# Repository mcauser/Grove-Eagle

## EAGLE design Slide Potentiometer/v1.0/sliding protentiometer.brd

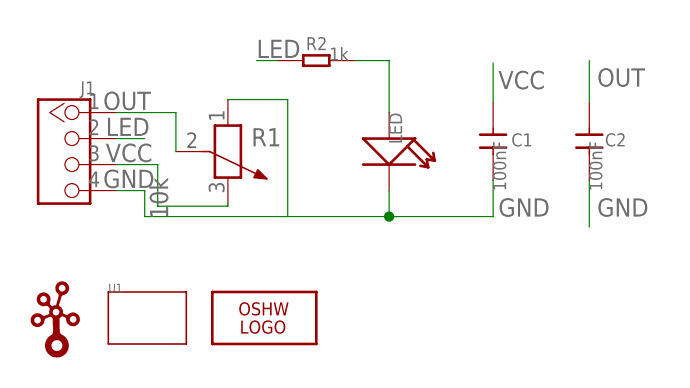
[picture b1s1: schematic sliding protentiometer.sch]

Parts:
C1, C2: 100nF; 0805
J1: TWIG-4P-2.0-2.0; 4P-2.0
LED: LED'0805'; LED-0805
LOGO1: LOGO-OSHW-FILLX0200-NT; OSHW_FILLX200_NOTEXT
R1: 10k; 3P-SQUA-45.6X10X5.8H
R2: 1k; 0805
U1: TWIG'3U'; 3U-DIM-W/-DRILL
U$1: LOGO-TWIG; TWIGLOGO

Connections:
GND: C1.2, C2.2, J1.4, LED.-, R1.1
LED: J1.2, R2.1
unnamed: LED.+, R2.2
OUT: C2.1, J1.1, R1.2 (3)
VCC: C1.1, J1.3, R1.3 (2)

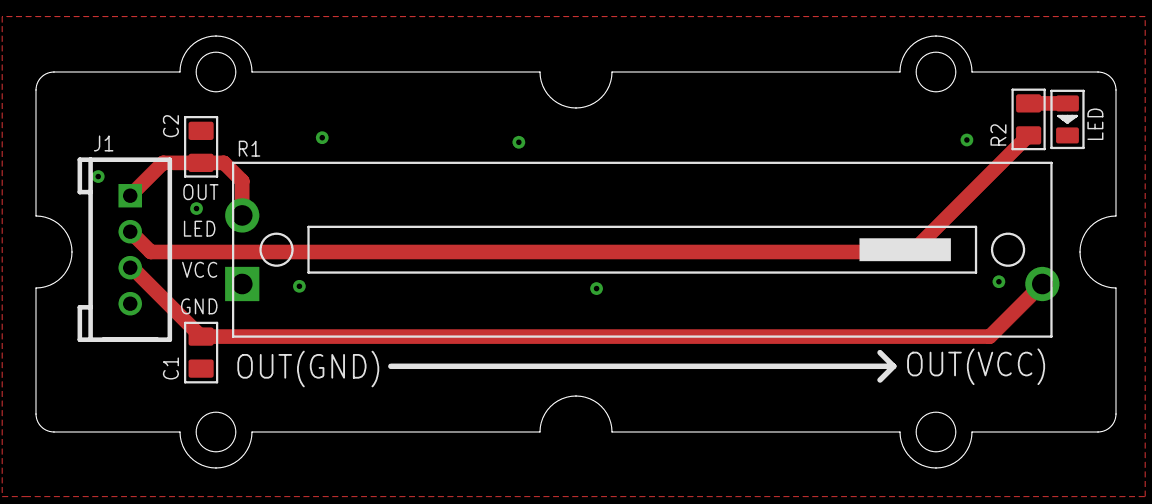
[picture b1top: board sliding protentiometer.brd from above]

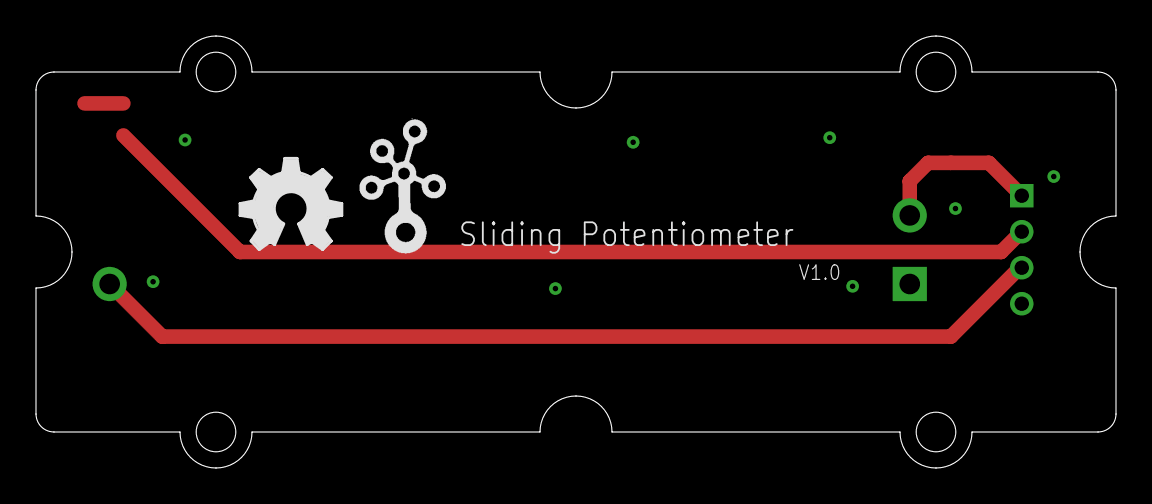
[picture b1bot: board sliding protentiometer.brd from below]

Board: 2 copper layers, 60.0 x 24.0 mm, 9 parts (2 on the bottom side), 5 nets.

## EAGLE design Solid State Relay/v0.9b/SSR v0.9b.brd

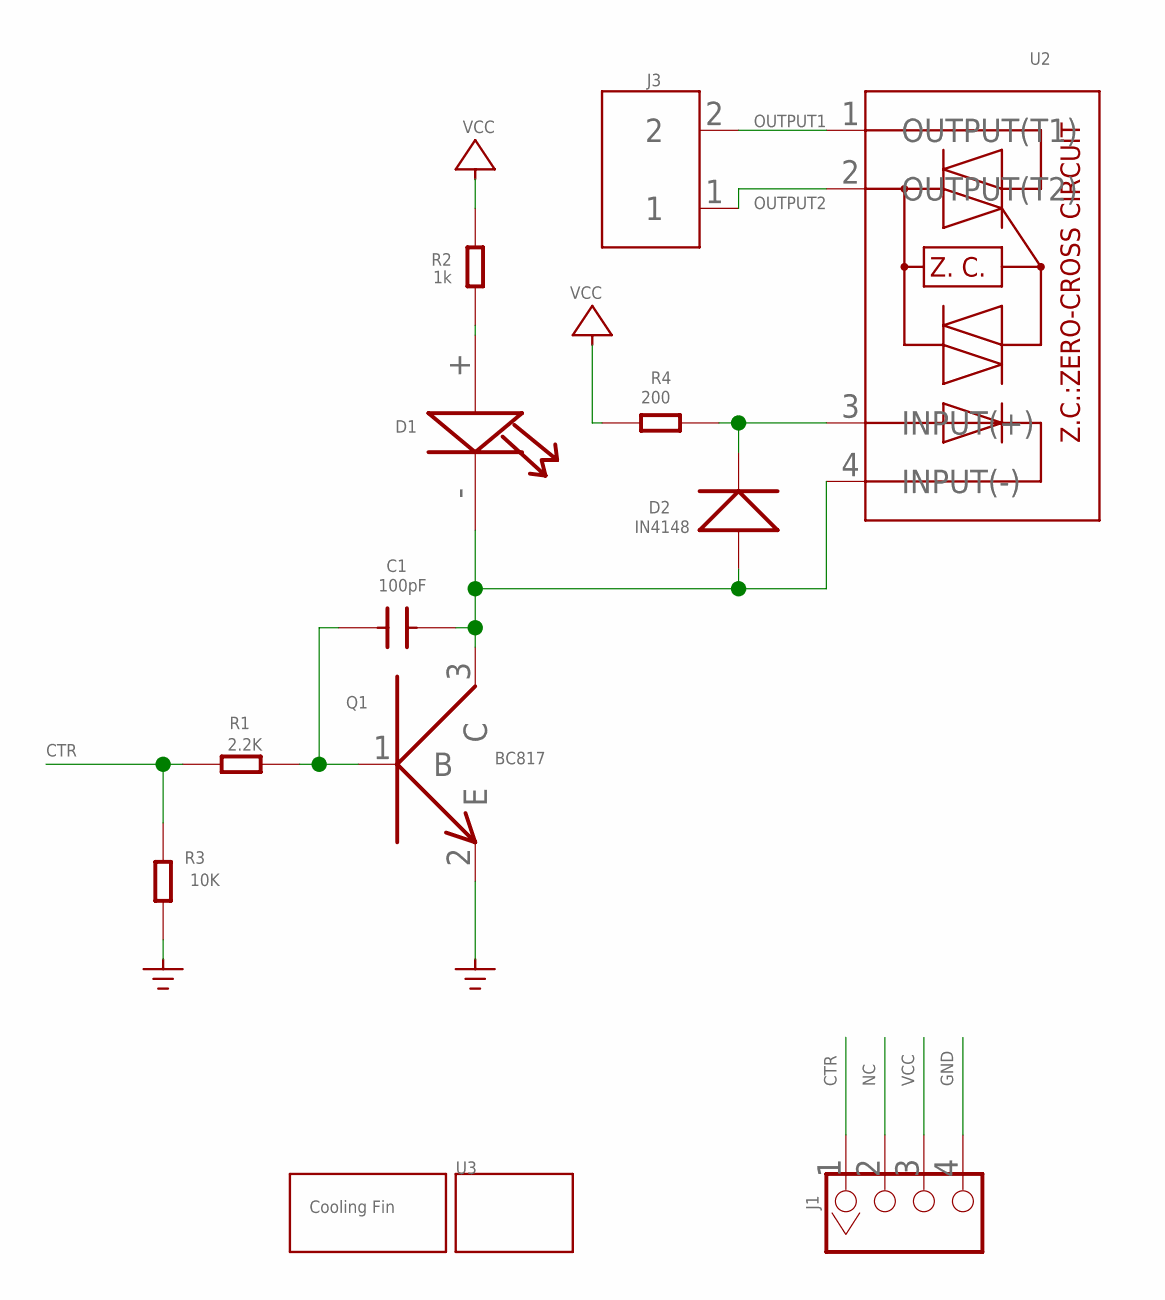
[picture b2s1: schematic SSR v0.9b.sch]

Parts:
C1: 100pF; 0603
D1: LED0805
D2: IN4148; DO-35-SMD
J1: TWIG-4P-2.0-2.0; 4P-2.0
J3: SCREW-TERMINAL-2P5.0; 2P-5.0
Q1: NPN_9013; SOT23
R1: 2.2K; 0603
R2: 1k; 0603
R3: 10K; 0603
R4: 200; 0603
U1: SILK-COOLING-FIN; COOLING-FIN-30X25
U2: RELAY-S208T02; 4P-23X4X16H
U3: TWIG-2X2U; 2X2U-DIM-W/-DRILL

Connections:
CTR: J1.1, R1.1, R3.2
GND: J1.4, Q1.2 (E), R3.1
unnamed: D2.C (-), R4.2, U2.3 (INPUT(+))
unnamed: C1.2, Q1.1 (B), R1.2
unnamed: C1.1, D1.-, D2.A (+), Q1.3 (C), U2.4 (INPUT(-))
unnamed: D1.+, R2.1
NC: J1.2
OUTPUT1: J3.2, U2.1 (OUTPUT(T1))
OUTPUT2: J3.1, U2.2 (OUTPUT(T2))
VCC: J1.3, R2.2, R4.1

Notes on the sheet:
BC817

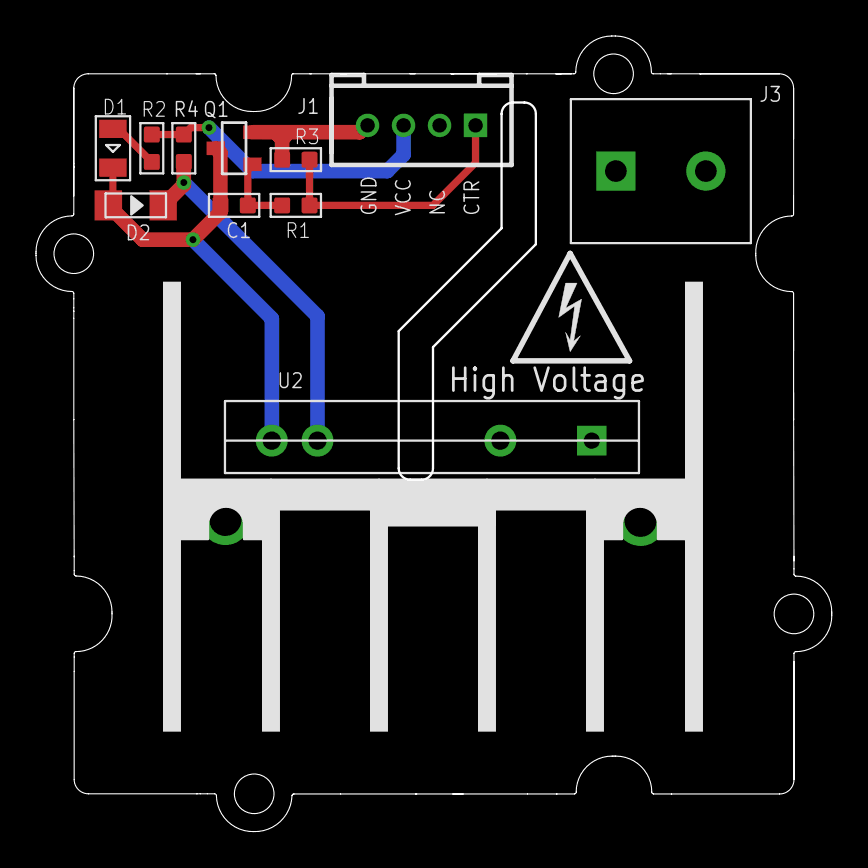
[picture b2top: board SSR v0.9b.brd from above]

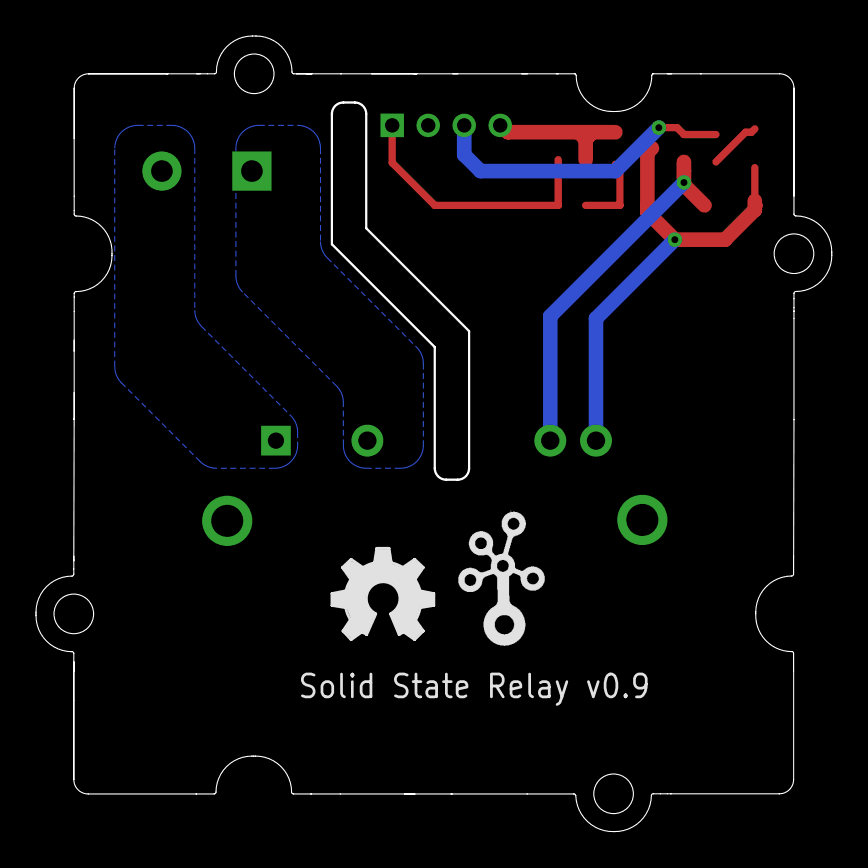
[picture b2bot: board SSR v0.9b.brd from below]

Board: 2 copper layers, 44.2 x 44.2 mm, 15 parts (2 on the bottom side), 9 nets.

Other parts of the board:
U$1: TWIGLOGO
U$2: OSHW_FILLX200_NOTEXT

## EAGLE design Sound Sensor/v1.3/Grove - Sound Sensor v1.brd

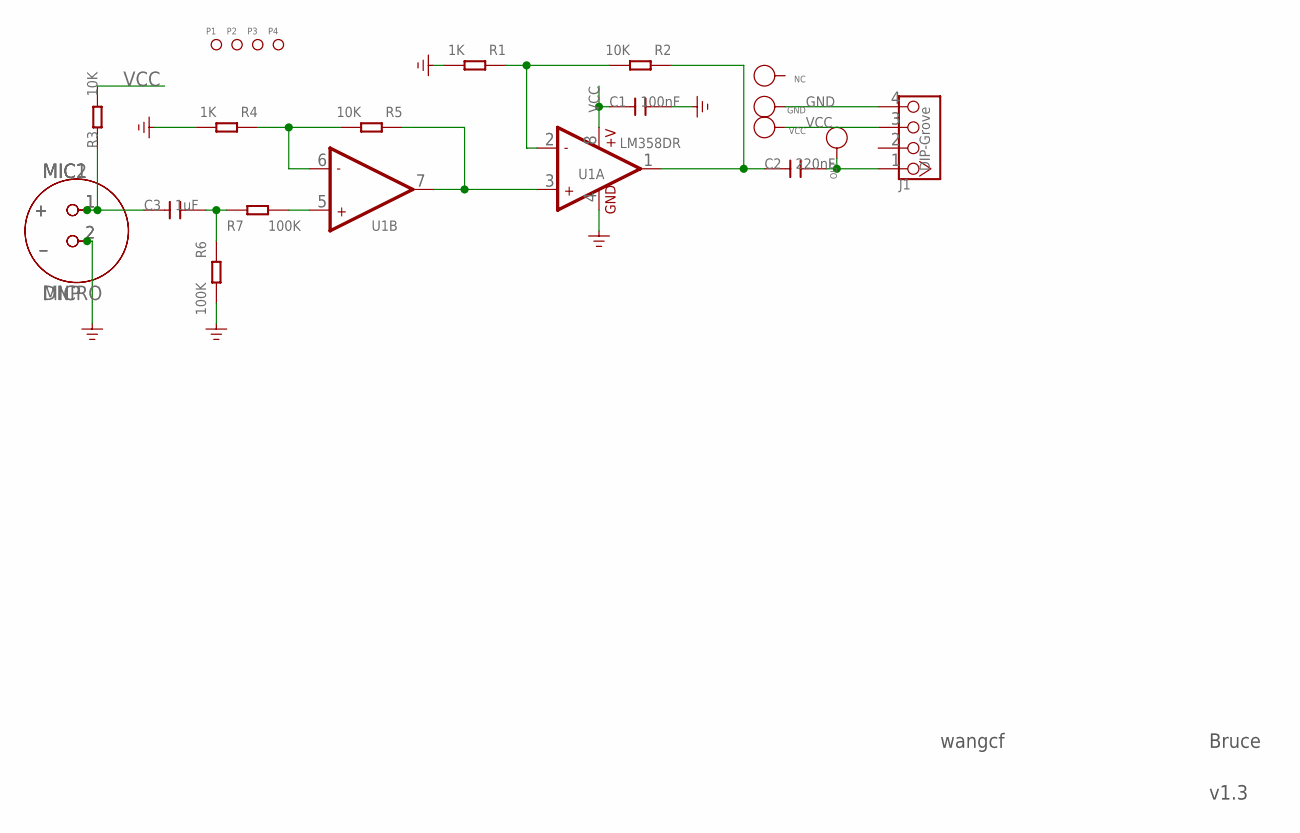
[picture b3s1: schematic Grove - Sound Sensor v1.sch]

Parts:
C1: 100nF; C0603
C2: 220nF; C0603
C3: 1uF; C0603
GND: PAD-TEST-POINT'4545'; TP_4545
J1: DIP-Grove; 4P-2.0
MIC1: MICRO
MIC2: DNP; MICRO
NC: PAD-TEST-POINT'4545'; TP_4545
OUT: PAD-TEST-POINT'4545'; TP_4545
P1, P2, P3, P4: PAD-MARK; ROUND-MARK-1.0
R1, R4: 1K; R0603
R2, R3, R5: 10K; R0603
R6, R7: 100K; R0603
U1: LM358DR; SO08
VCC: PAD-TEST-POINT'4545'; TP_4545

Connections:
GND: C1.2, GND.T, J1.4, MIC1.2 (_), MIC2.2 (_), R1.2, R4.2, R6.2, U1.4 (GND)
unnamed: R7.2, U1.5 (+IN2)
unnamed: R4.1, R5.2, U1.6 (-IN2)
unnamed: C3.2, R6.1, R7.1
unnamed: C3.1, MIC1.1 (+), MIC2.1 (+), R3.1
unnamed: R5.1, U1.3 (+IN1), U1.7 (OUT2)
unnamed: R1.1, R2.2, U1.2 (-IN1)
OUT: C2.2, J1.1, OUT.T
OUT1: C2.1, R2.1, U1.1 (OUT1)
VCC: C1.1, J1.3, R3.2, U1.8 (+V), VCC.T

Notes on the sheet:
wangcf
Bruce
v1.3

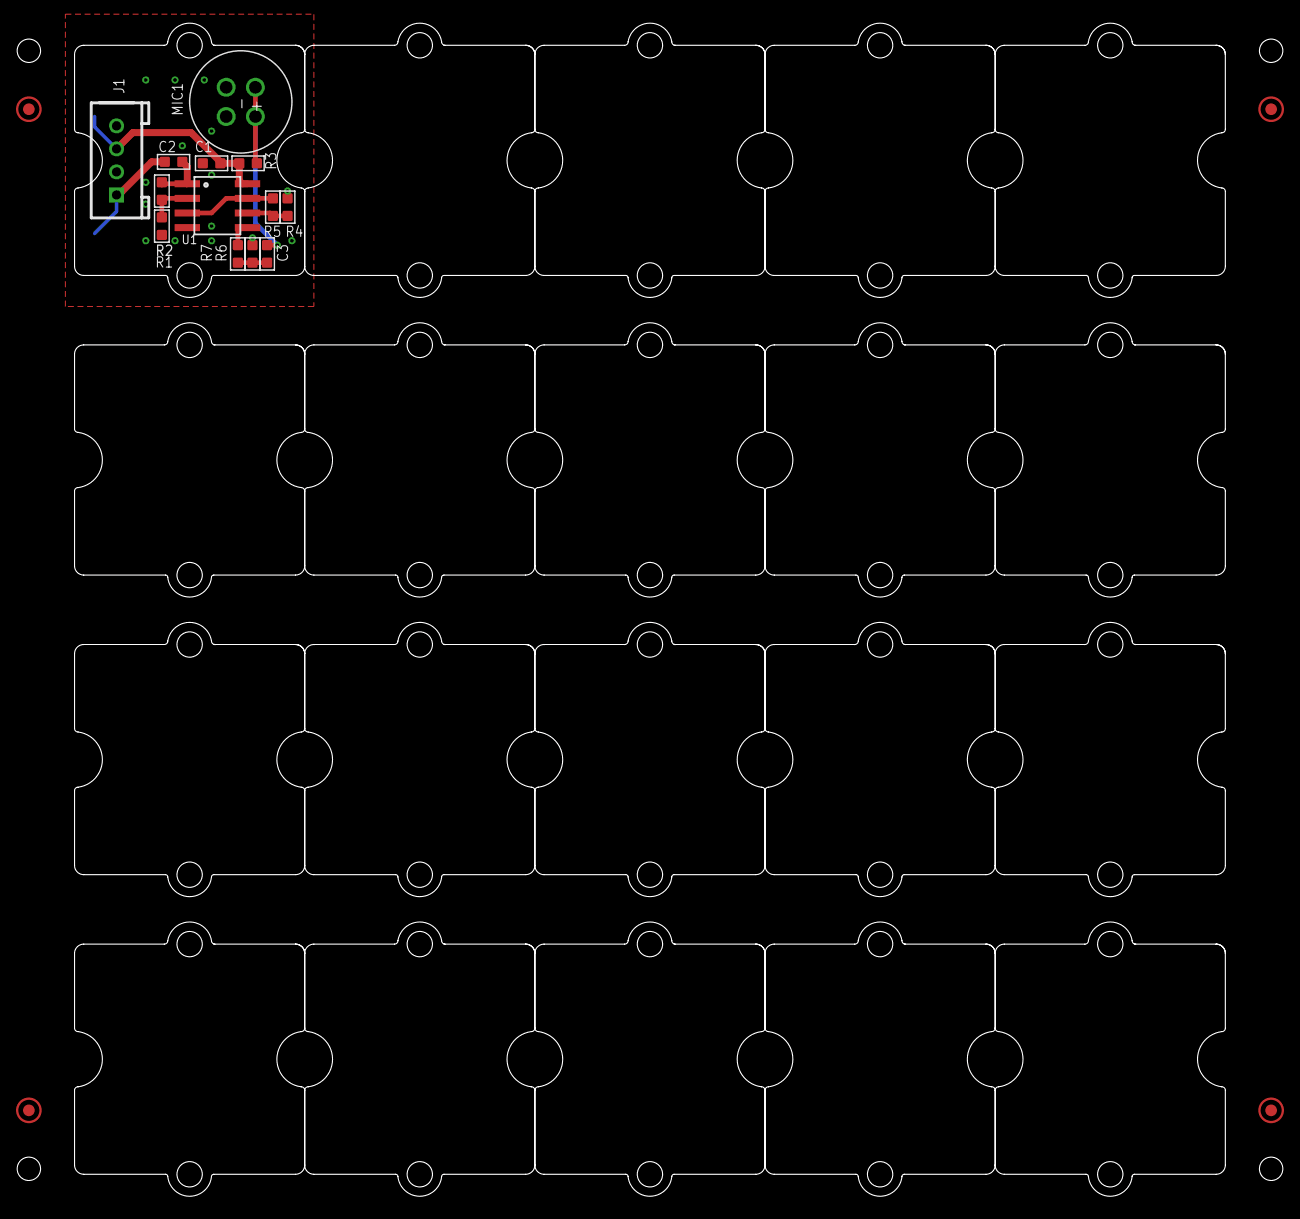
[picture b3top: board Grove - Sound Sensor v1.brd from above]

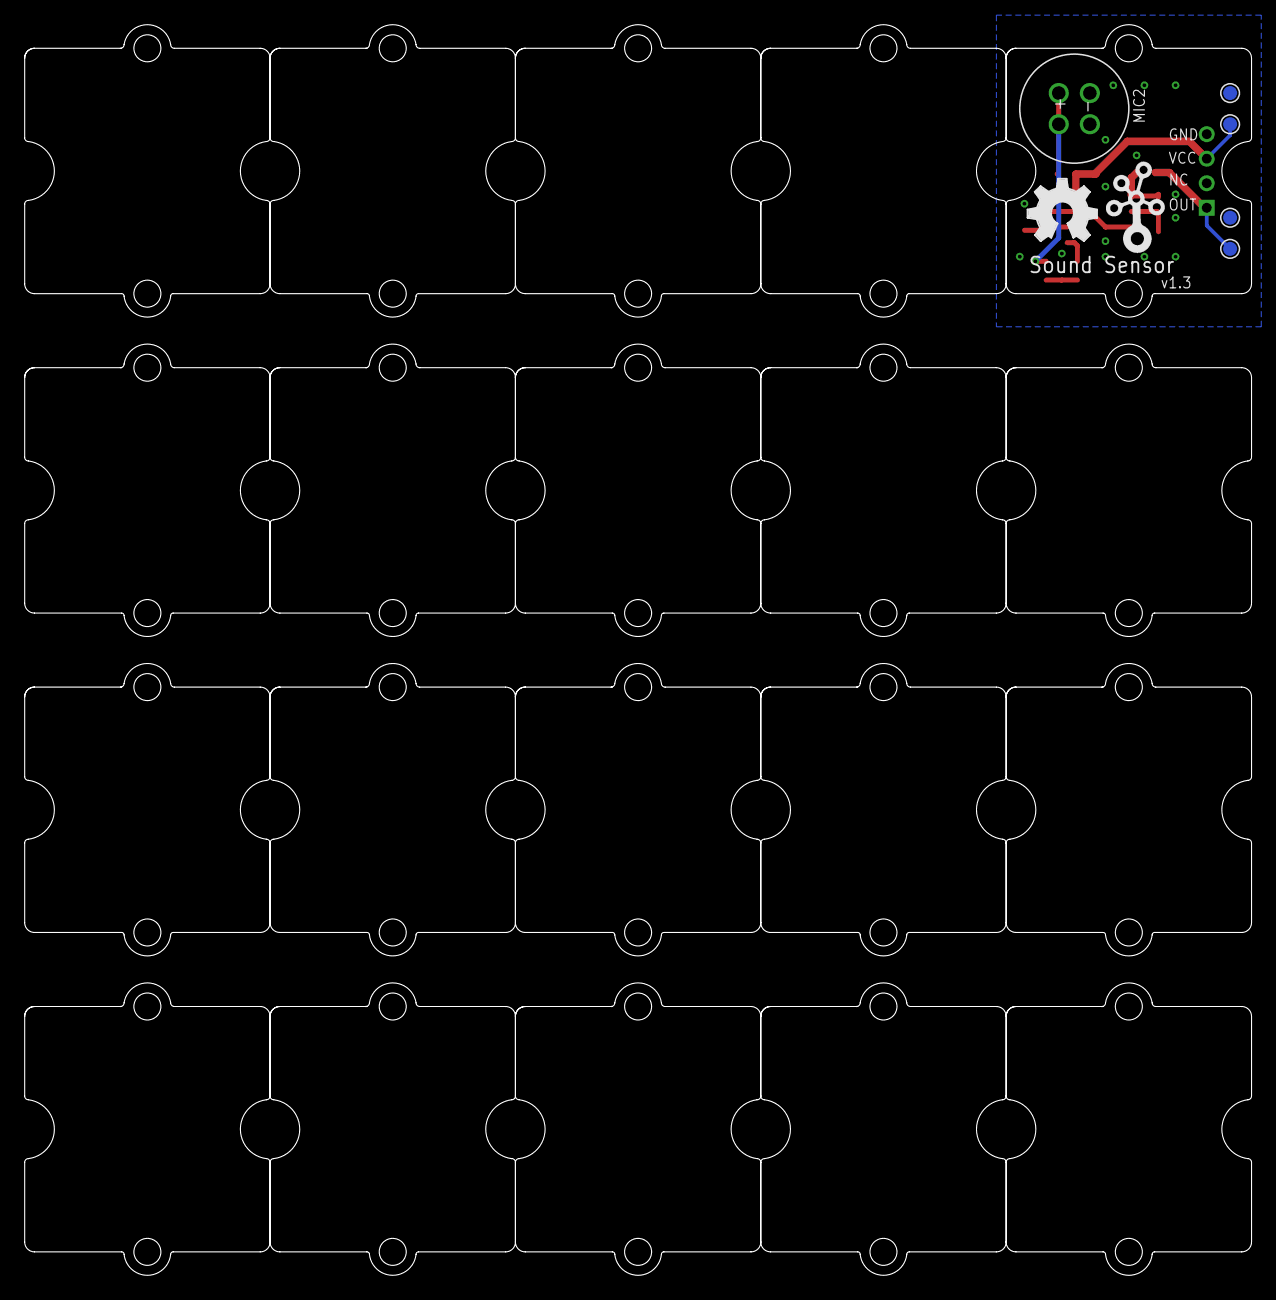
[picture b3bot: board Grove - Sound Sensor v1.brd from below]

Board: 2 copper layers, 100.0 x 101.9 mm, 44 parts (7 on the bottom side), 10 nets.

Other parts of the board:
U$1: OSHW_FILLX200_NOTEXT
U$4, U$12, U$13, U$14, U$15, U$16, U$17, U$18, U$19, U$20, U$21, U$22, U$23, U$24, U$25, U$26, U$27, U$28, U$29, U$30: 1U-DIM-W/-DRILL
U$7: TWIGLOGO

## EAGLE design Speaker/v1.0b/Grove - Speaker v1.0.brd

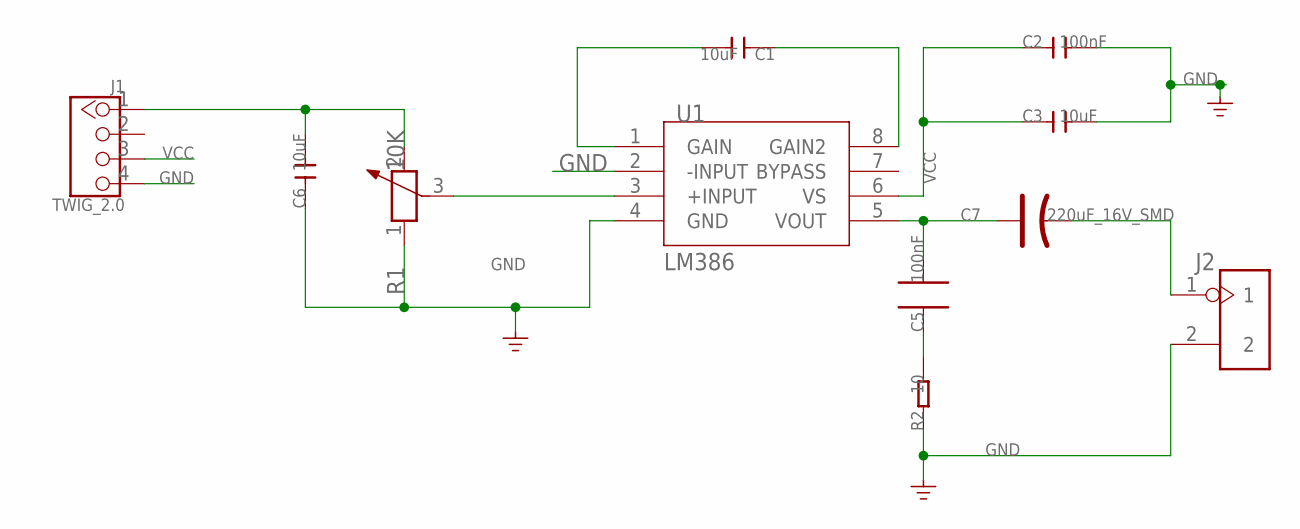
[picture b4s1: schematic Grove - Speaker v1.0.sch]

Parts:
C1, C3, C6: 10uF; C0805
C2: 100nF; C0603
C5: 100nF; 0603
C7: 220uF_16V_SMD; ELECTRO-SMD-E-7.8MM
J1: TWIG_2.0; 2.0_1X4
J2: HEADER-2P-2.0; 2P-2.0
R1: 10K; 3P-SQUA-7X6.8
R2: 10; R0603
U1: LM386; SO08

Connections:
GND: C2.2, C3.2, C6.1, J1.4, J2.2, R1.1, R2.1, U1.2 (-INPUT), U1.4 (GND)
unnamed: C5.1, R2.2
unnamed: C1.1, U1.8 (GAIN2)
unnamed: C7.-, J2.1
unnamed: R1.3, U1.3 (+INPUT)
unnamed: C6.2, J1.1, R1.2
unnamed: C5.2, C7.+, U1.5 (VOUT)
unnamed: C1.2, U1.1 (GAIN)
VCC: C2.1, C3.1, J1.3, U1.6 (VS)

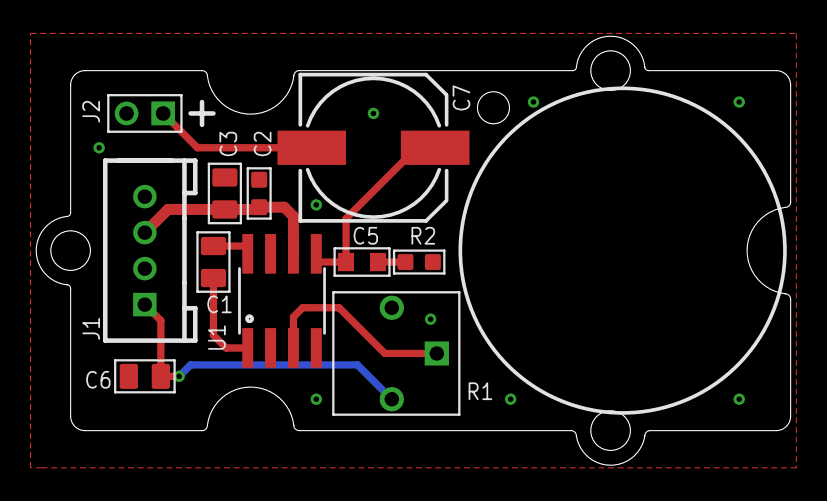
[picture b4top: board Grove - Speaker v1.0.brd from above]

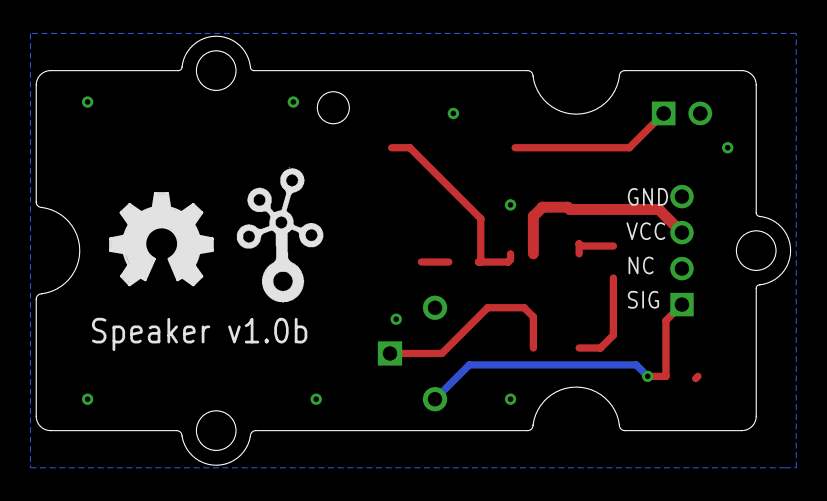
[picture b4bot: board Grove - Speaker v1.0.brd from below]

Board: 2 copper layers, 41.9 x 23.8 mm, 14 parts (2 on the bottom side), 9 nets.

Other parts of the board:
U$2: 2U-DIM-W/DRILL
U$3: OSHW_FILLX200_NOTEXT
U$4: TWIGLOGO

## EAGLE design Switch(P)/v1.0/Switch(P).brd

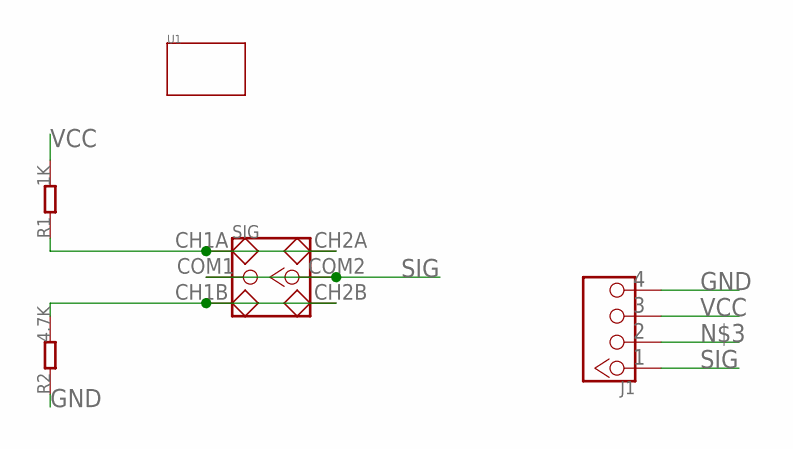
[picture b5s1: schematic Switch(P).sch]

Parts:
J1: TWIG-4P-2.0-2.0; 4P-2.0
R1: 1K; 0603
R2: 4.7K; 0603
SIG: SWITCH-2CH-6P; 6P-2CH-2.54-7.6X3.0
U1: TWIG-1U; 1U-DIM-W/-DRILL

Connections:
GND: J1.4, R2.1
unnamed: R1.1, SIG.CH1A, SIG.CH2A
unnamed: R2.2, SIG.CH1B, SIG.CH2B
SIG: J1.1, SIG.COM1, SIG.COM2
VCC: J1.3, R1.2

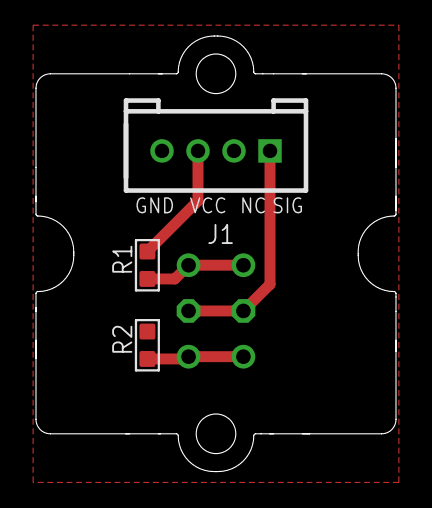
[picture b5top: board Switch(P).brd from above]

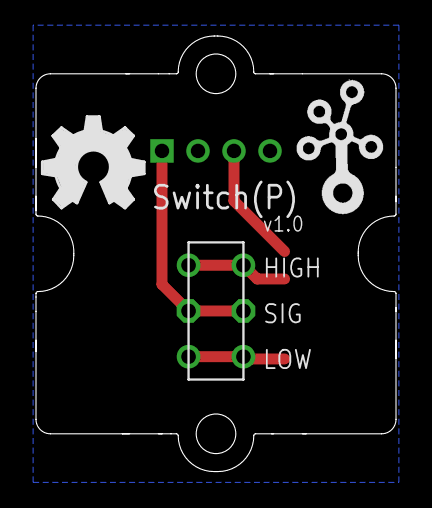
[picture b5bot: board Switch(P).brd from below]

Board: 2 copper layers, 20.0 x 24.2 mm, 7 parts (3 on the bottom side), 5 nets.

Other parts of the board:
U$1: TWIGLOGO
U$2: OSHW_FILLX200_NOTEXT

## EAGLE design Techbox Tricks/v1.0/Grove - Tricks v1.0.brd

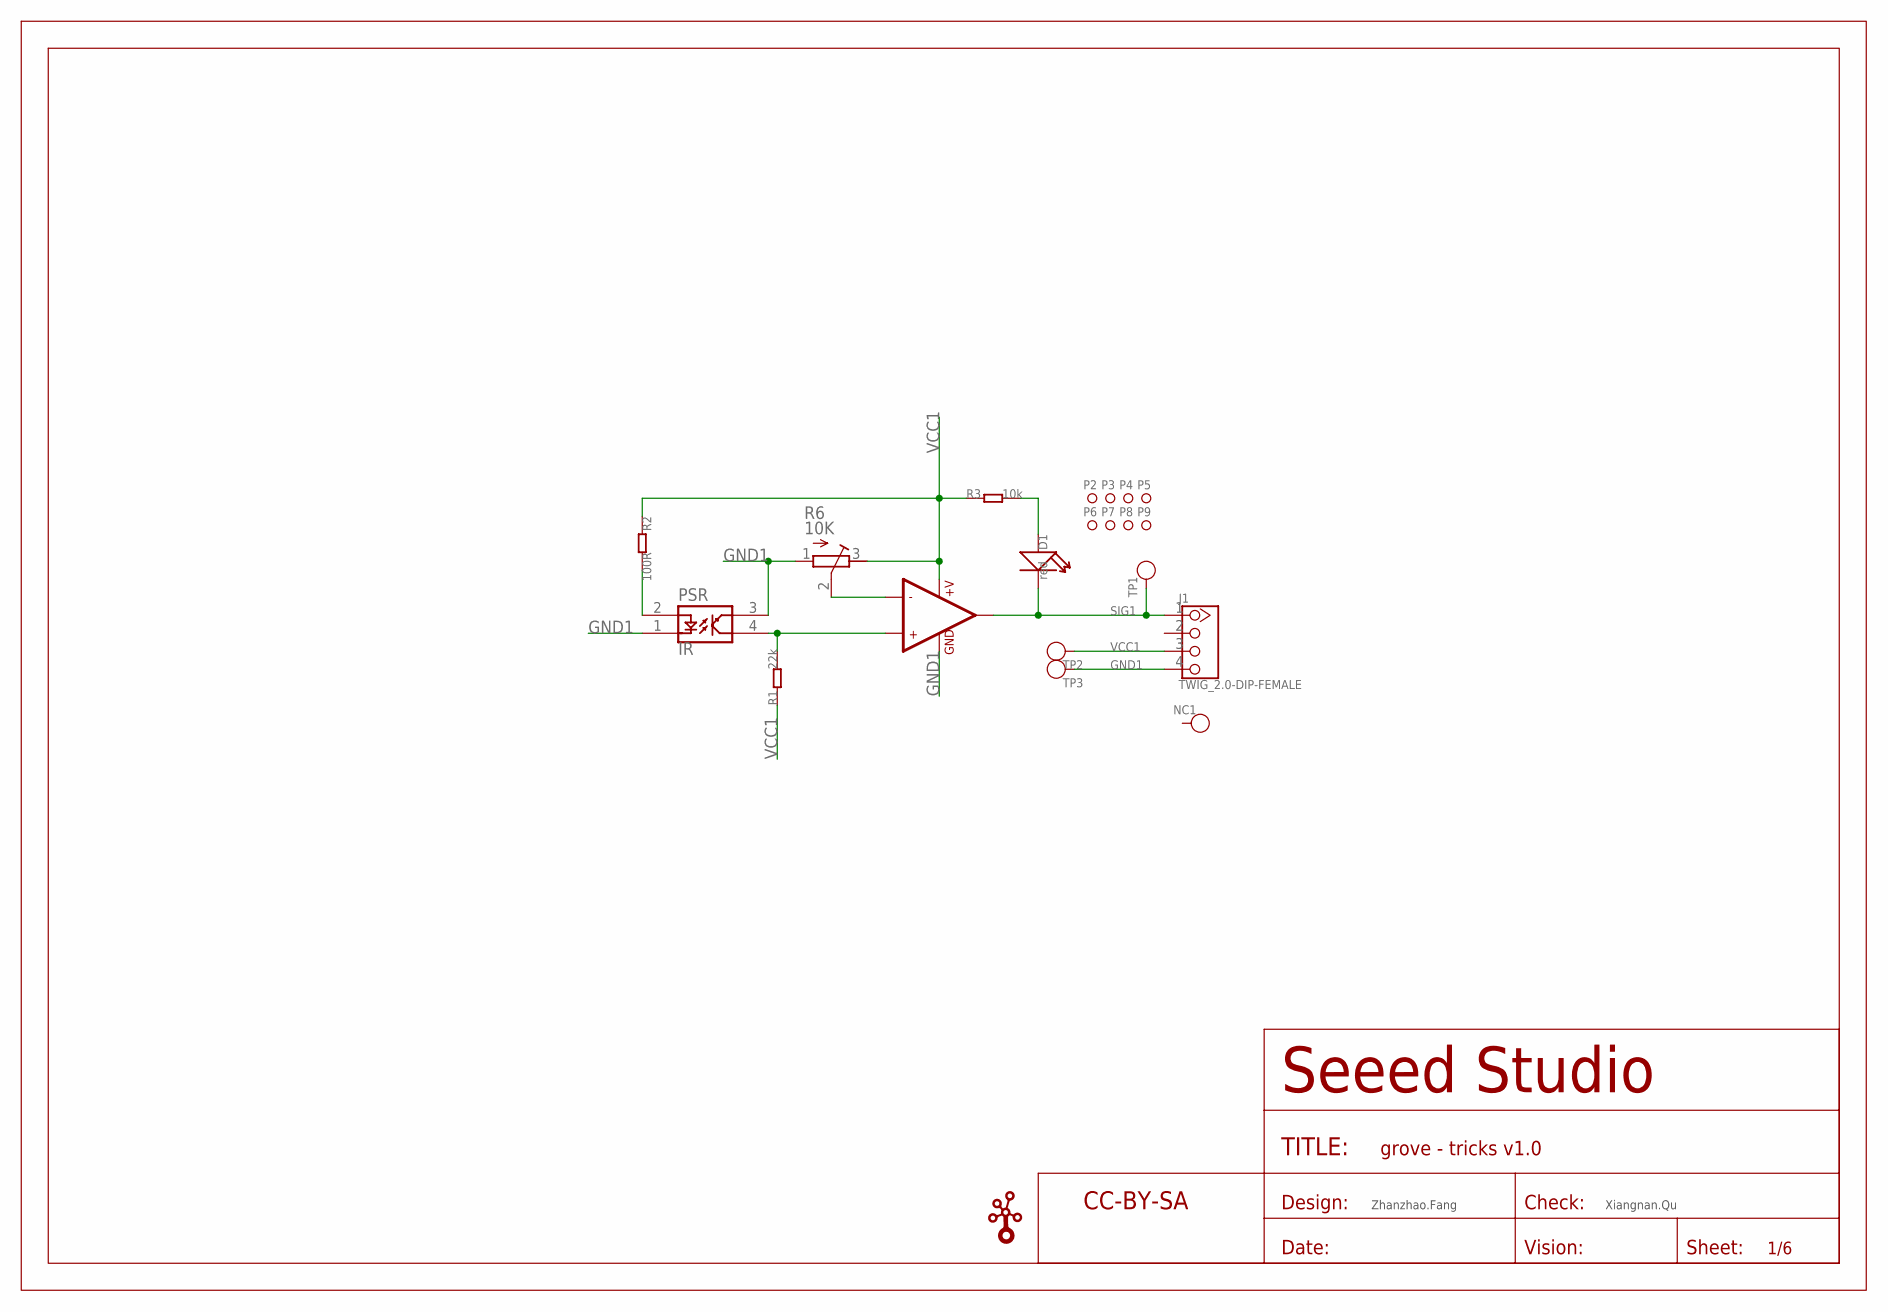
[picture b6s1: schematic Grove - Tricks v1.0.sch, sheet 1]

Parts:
D1: red; LED0603
J1: TWIG_2.0-DIP-FEMALE; 2.0_1X4
NC1: TEST-POINT'4545'; TP-D45MIL
P2, P3, P4, P5, P6, P7, P8, P9: MARK-1.0'ANNULAR'; ROUND-MARK-1.0
PSR: PSR
R1: 22k; 0603_S
R2: 100R; 0603_S
R3: 10k; 0603_S
R6: 10K; RTRIM3214W
TP1, TP2, TP3: TEST-POINT'4545'; TP-D45MIL
U1: 002-LMV358; SO08
U$2: TWIGLOGOTWIGLOGO_SMALL; TWIGLOGO_SMALL
U$3: SEEEDSTUDIO-OPEN-SCH-FRAME; SEEEDSTUDIO-PCB-FRAME

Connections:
GND1: J1.4, PSR.1, PSR.3, R6.1 (E), TP3.T, U1.4 (GND)
unnamed: R6.2 (S), U1.2 (-IN1)
unnamed: PSR.4, R1.2, U1.3 (+IN1)
unnamed: PSR.2, R2.2
unnamed: D1.1 (+), R3.2
SIG1: D1.2 (-), J1.1, TP1.T, U1.1 (OUT1)
VCC1: J1.3, R1.1, R2.1, R3.1, R6.3 (A), TP2.T, U1.8 (+V)

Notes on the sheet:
Zhanzhao.Fang
Xiangnan.Qu

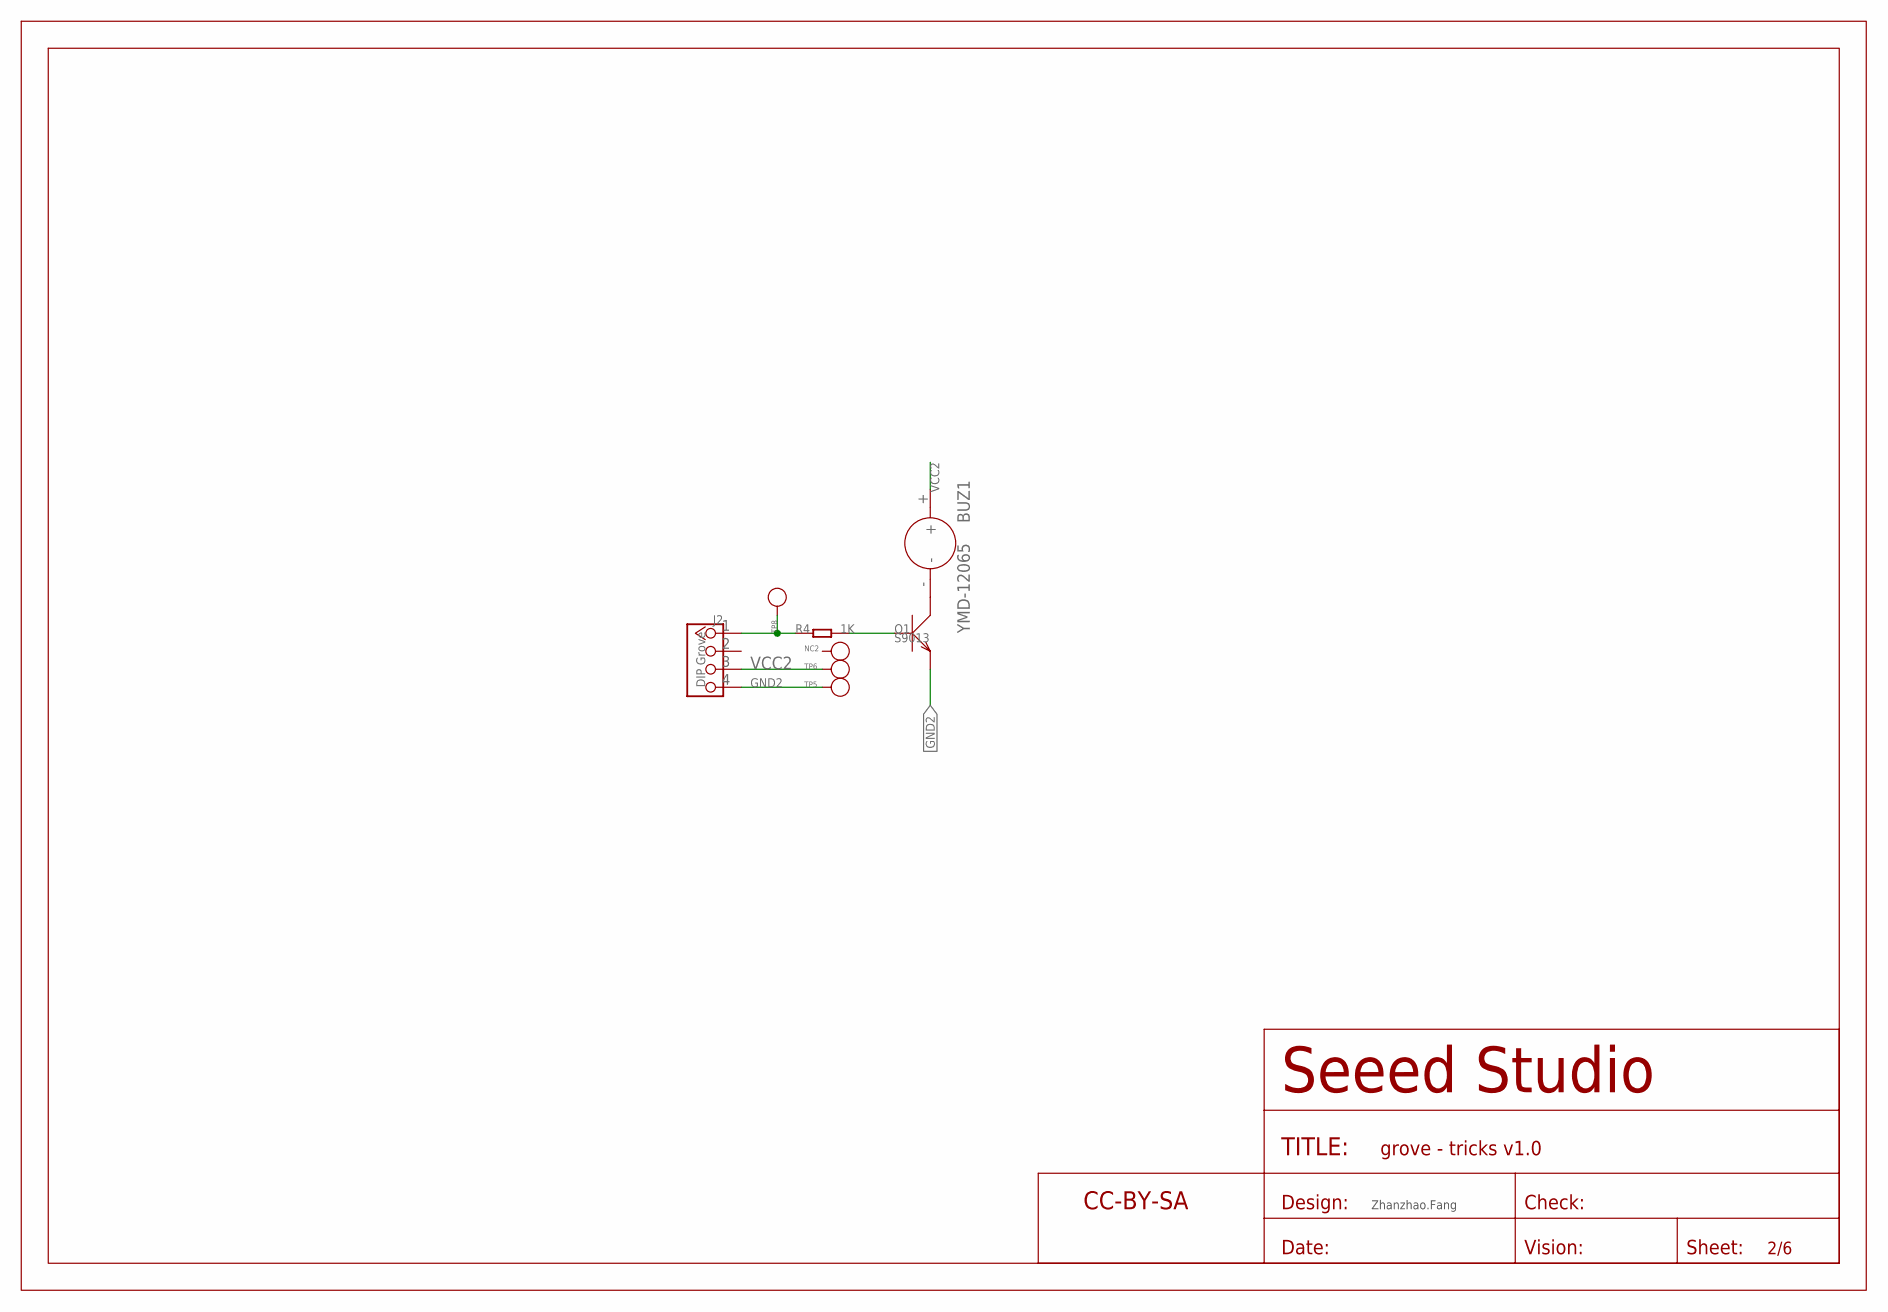
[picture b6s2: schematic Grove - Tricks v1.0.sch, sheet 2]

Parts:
BUZ1: YMD-12065; 2P-7.6-D12X6.5H
J2: DIP Grove; 4P-2.0
NC2: PAD-TEST-POINT'4545'; TP_4545
Q1: S9013; SOT23
R4: 1K; R0603
TP5, TP6, TP8: PAD-TEST-POINT'4545'; TP_4545
U$6: SEEEDSTUDIO-OPEN-SCH-FRAME; SEEEDSTUDIO-PCB-FRAME

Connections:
GND2: J2.4, Q1.2 (E), TP5.T
unnamed: Q1.1 (B), R4.2
unnamed: BUZ1.-, Q1.3 (C)
unnamed: J2.1, R4.1, TP8.T
VCC2: BUZ1.+, J2.3, TP6.T

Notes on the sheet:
Zhanzhao.Fang

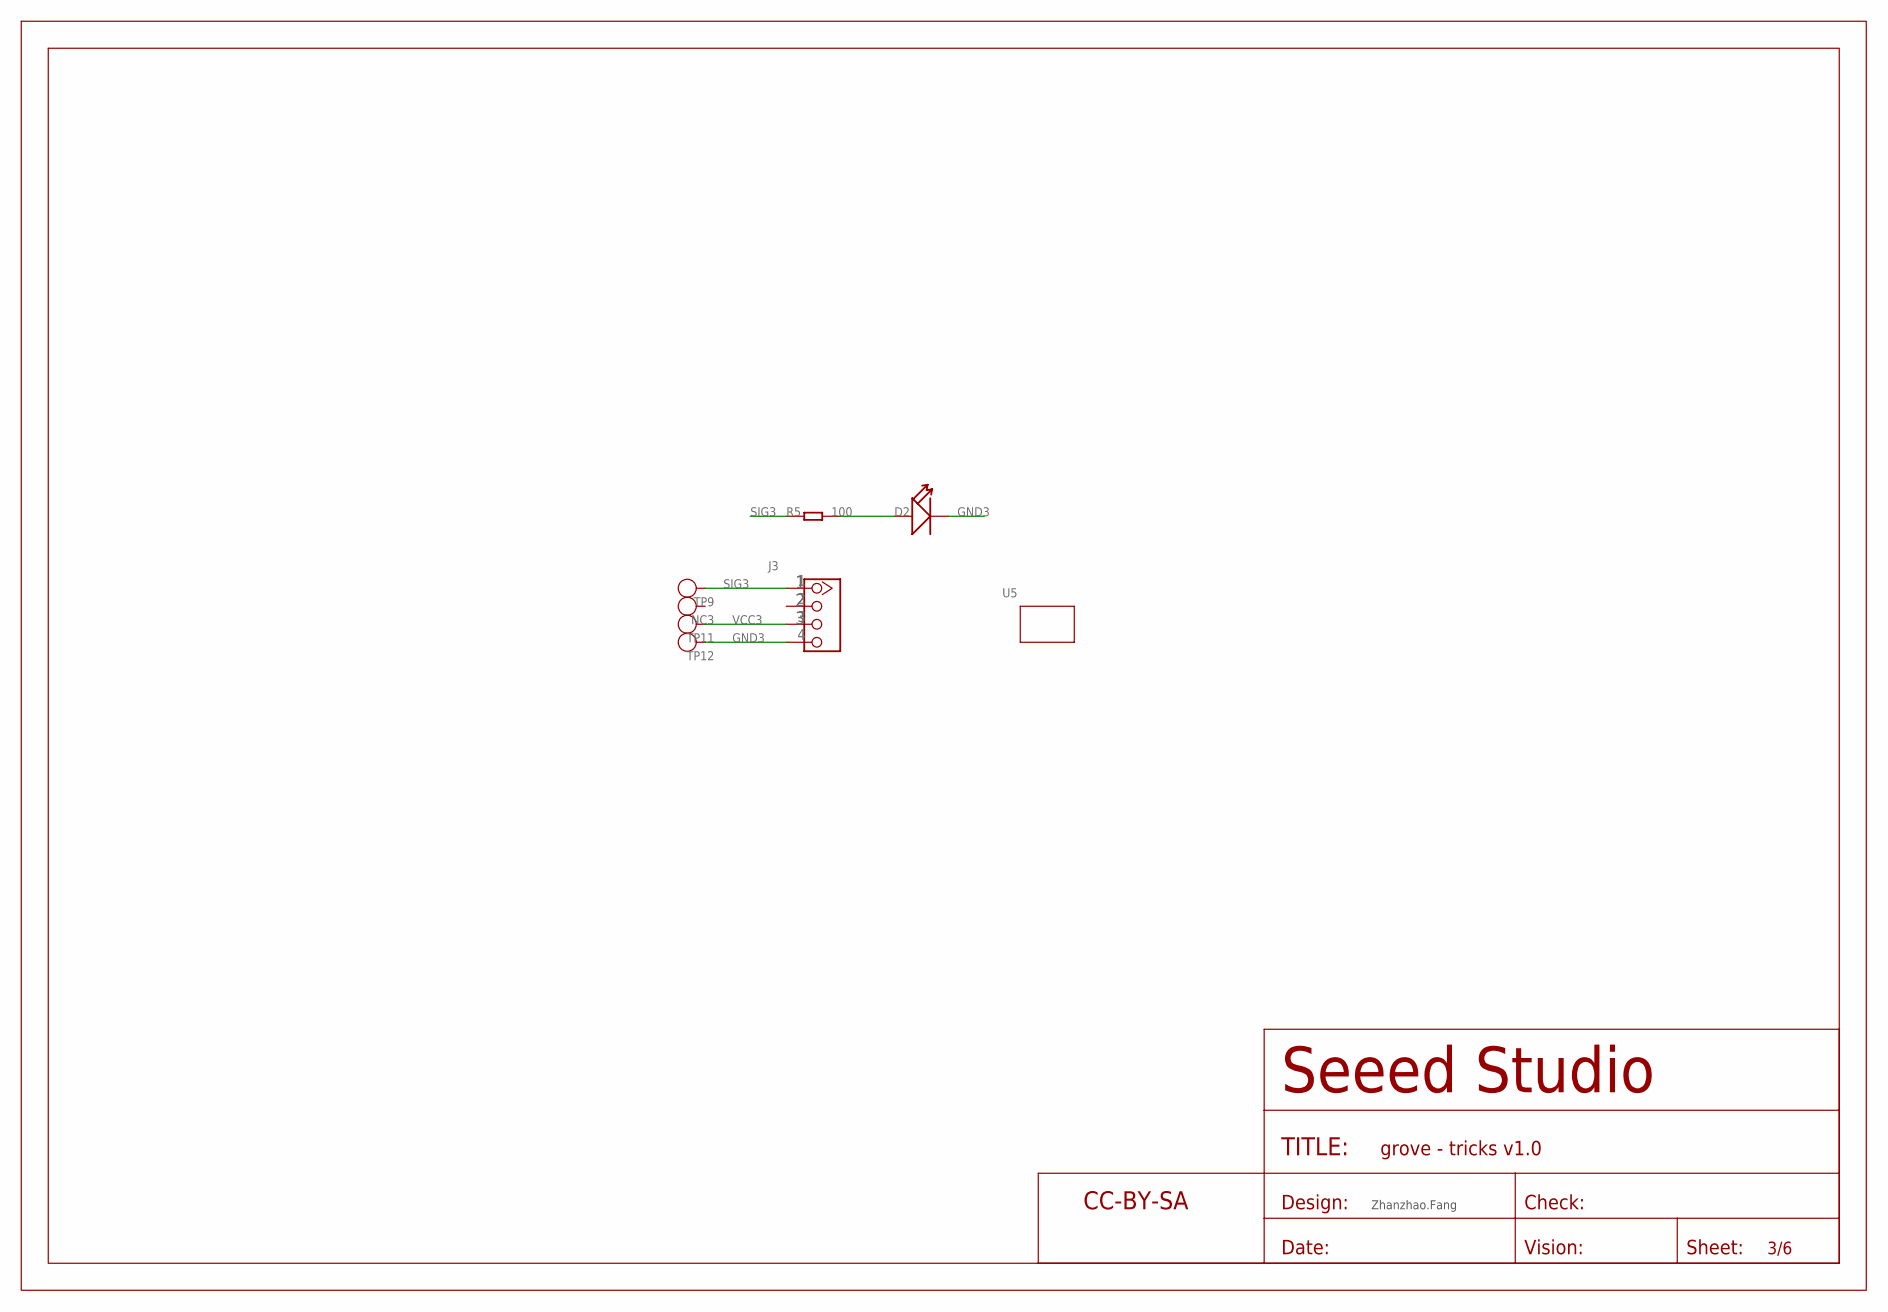
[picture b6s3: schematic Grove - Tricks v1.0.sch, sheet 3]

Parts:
D2: LED-3MM; LED-2P-2.54-3MM
J3: GROVE-CONNECTOR-DIP-2.0; HW4-2.0
NC3: TEST-POINT'4545'; TP-D45MIL
R5: 100; R1206
TP9, TP11, TP12: TEST-POINT'4545'; TP-D45MIL
U5: GROVE; GROVE-1*1-TEST-PLATFORM-LED
U$4: SEEEDSTUDIO-OPEN-SCH-FRAME; SEEEDSTUDIO-PCB-FRAME

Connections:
GND3: D2.K (-), J3.4, TP12.T
unnamed: D2.A (+), R5.2
SIG3: J3.1, R5.1, TP9.T
VCC3: J3.3, TP11.T

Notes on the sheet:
Zhanzhao.Fang

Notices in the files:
parts and their libraries:
moudle-new: This work is licensed under the Creative Commons Attribution 4.0 International License.
To view a copy of this license,visit:
http://creativecommons.org/licenses/by-sa/4.0
moudle-new: CC-BY-SA
